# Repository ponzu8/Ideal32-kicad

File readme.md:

症状としましては
R=L10=K02
S=L12=K09
C=L13=K12
U=R10
L=R12
N=R13
この6つのキーが反応しない状態です。
手元にテスタ―がないため導通もできない状況です、申し訳ございません。
今回設計など初めてのことで回路図とpcbnewをうまく作成することができずごちゃごちゃになっています。
他人任せとなってしまい大変申し訳ないのですがよろしくお願いいたします。
できれば何かお礼でもさせていただければと思っております。
お手数おかけしてしまい、大変申し訳ございません。

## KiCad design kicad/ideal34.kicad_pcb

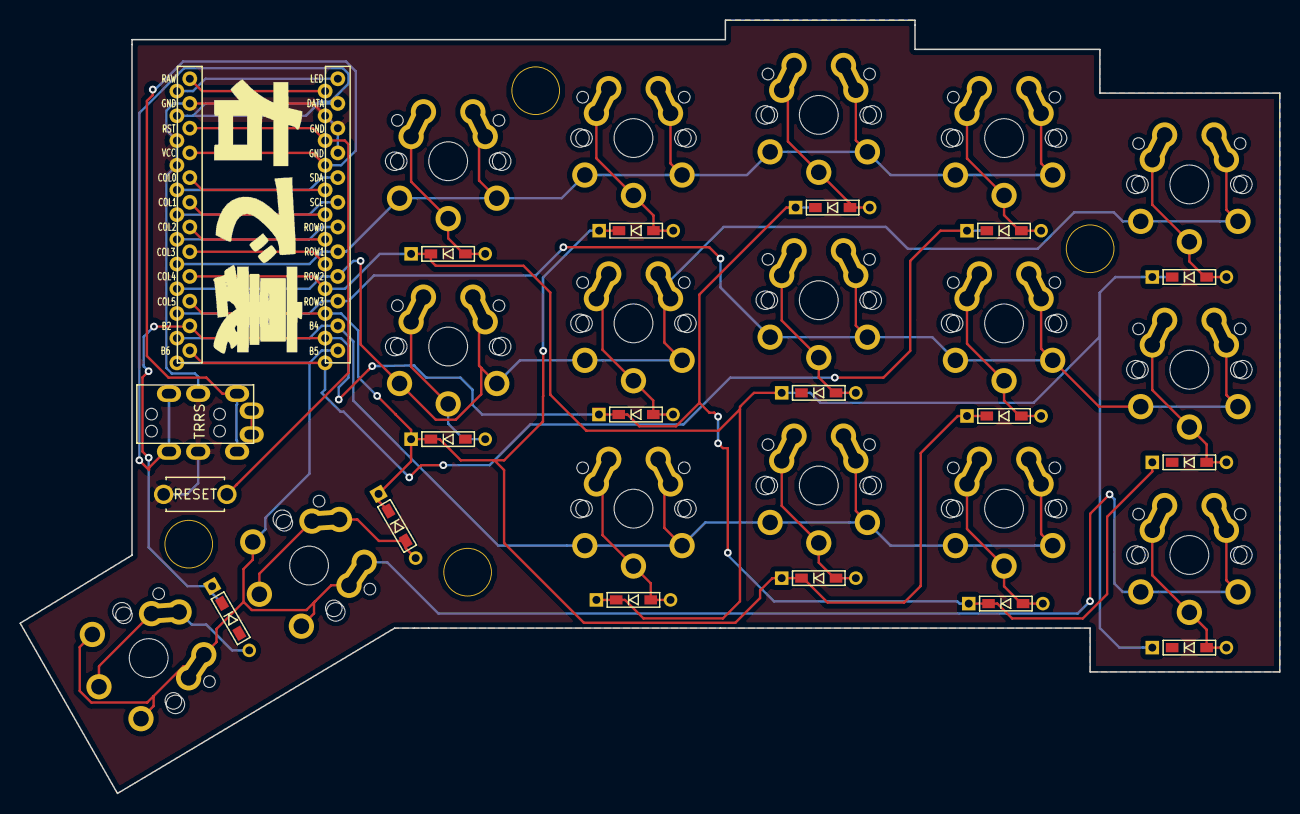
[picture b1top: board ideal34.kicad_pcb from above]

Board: 2 copper layers, 129.5 x 79.5 mm, 39 parts (0 on the bottom side), 29 nets.

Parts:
D1, D2, D3, D4, D5, D6, D7, D8, D9, D10, D11, D12, D13, D14, D15, D16: D_Small; D3_TH_SMD
J1: MJ-4PP-9
K1, K2, K3, K4, K5, K6, K7, K8, K9, K10, K11, K12, K13, K14, K15, K16: KEYSW; key_switch
Ref**: Val**; HOLE
Ref**#2, Ref**#3, Ref**#4: Val**; HOLE
SW1: SW_PUSH; ResetSW
U1: ProMicro; ProMicro_v2

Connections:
+5V: J1.C, SW1.2, U1.3, U1.4, U1.23
unnamed: D1.2, K1.1
unnamed: D2.2, K2.1
unnamed: D3.2, K3.1
unnamed: D4.2, K4.1
unnamed: D5.2, K5.1
unnamed: D6.2, K6.1
unnamed: D7.2, K7.1
unnamed: D8.2, K8.1
unnamed: D9.2, K9.1
unnamed: D10.2, K10.1
unnamed: D11.2, K11.1
unnamed: D12.2, K12.1
unnamed: D13.2, K13.1
unnamed: D14.2, K14.1
unnamed: D15.2, K15.1
unnamed: D16.2, K16.1
RST: SW1.1, U1.22
VCC: J1.D, U1.21
col0: K1.2, K2.2, K3.2, K4.2, U1.8
col1: K5.2, K6.2, K7.2, U1.9
col2: K8.2, K9.2, K10.2, U1.10
col3: K11.2, K12.2, K13.2, U1.11
col4: K14.2, K15.2, K16.2, U1.12
data: J1.B, U1.2
row0: D1.1, D5.1, D8.1, D11.1, D14.1, U1.16
row1: D2.1, D6.1, D9.1, D12.1, D15.1, U1.15
row2: D3.1, D7.1, D10.1, D13.1, D16.1, U1.14
row3: D4.1, U1.13
